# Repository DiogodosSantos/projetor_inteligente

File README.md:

# projetor_inteligente
Arquivos importantes e códigos-fonte do trabalho de conclusao de curso: Firefly.

Criadores:  Diogo Batista dos Santos & Eric Nozomi Tatsuta

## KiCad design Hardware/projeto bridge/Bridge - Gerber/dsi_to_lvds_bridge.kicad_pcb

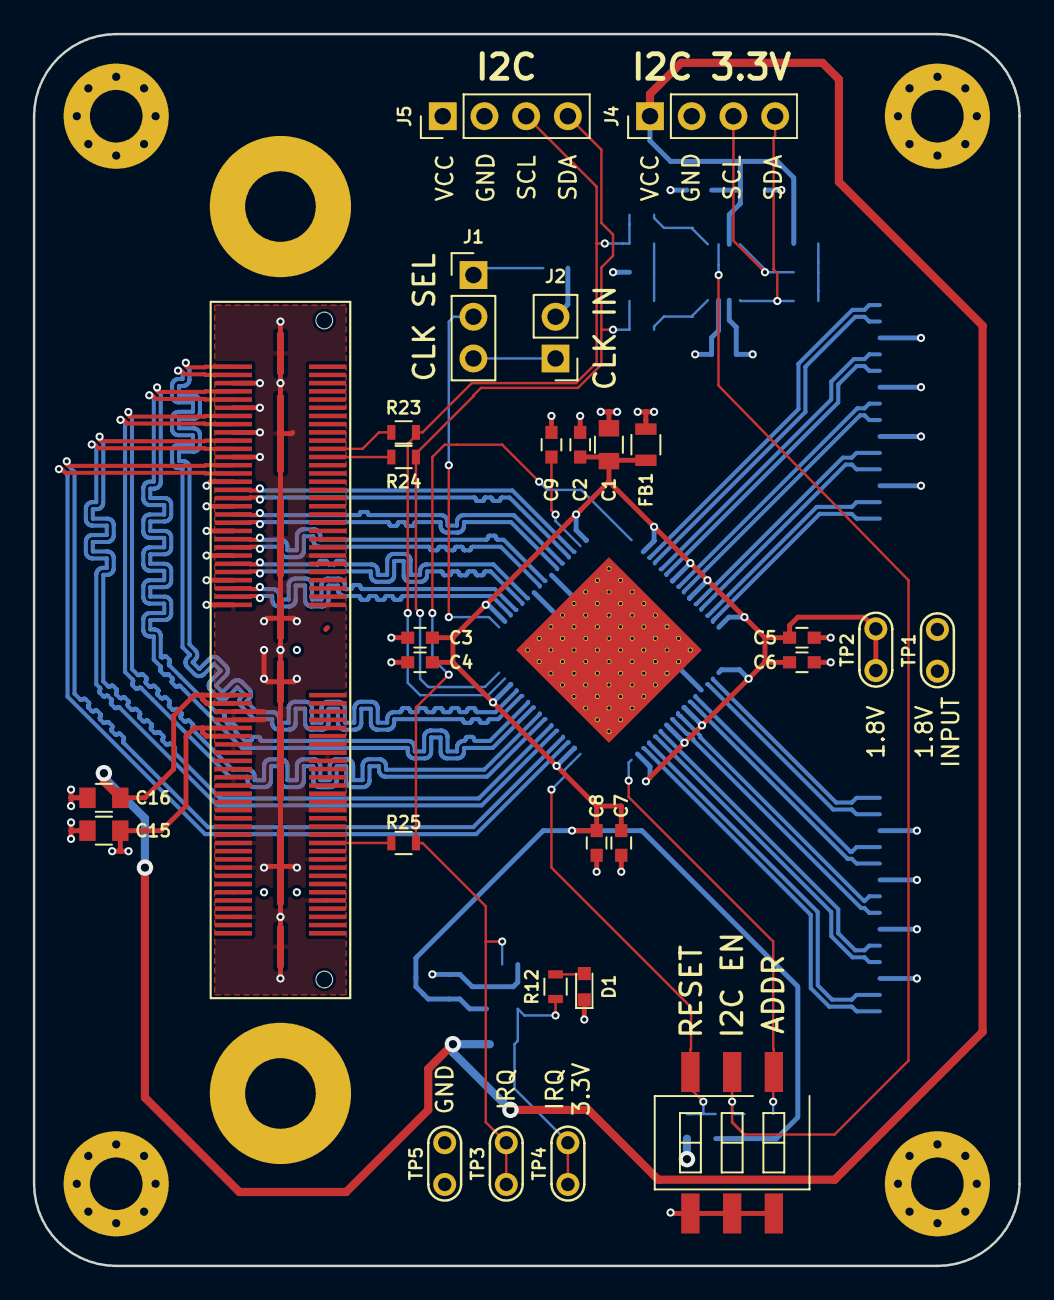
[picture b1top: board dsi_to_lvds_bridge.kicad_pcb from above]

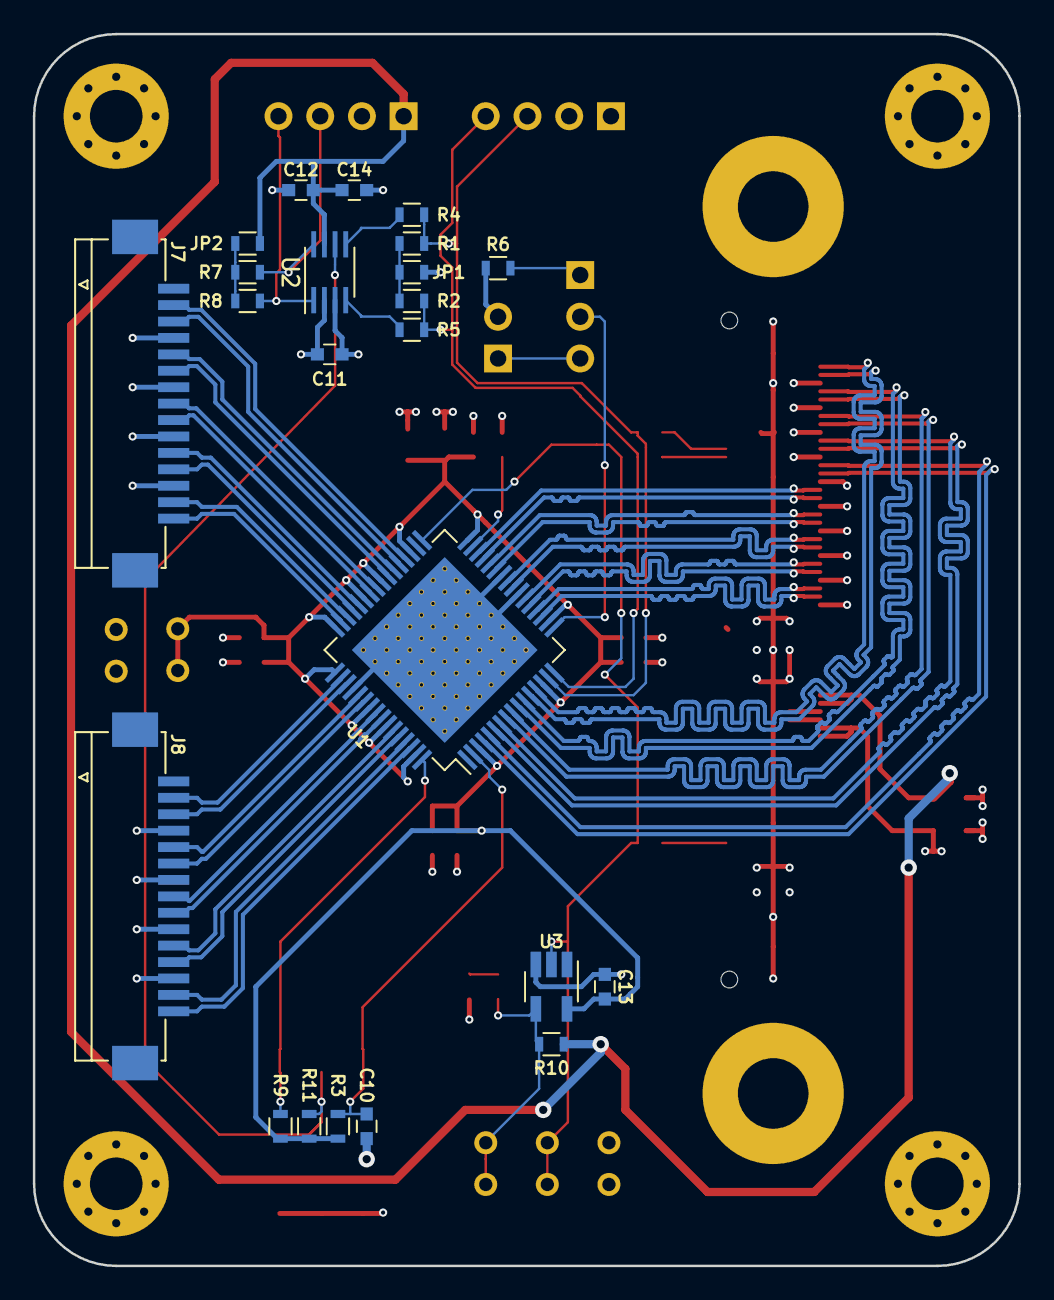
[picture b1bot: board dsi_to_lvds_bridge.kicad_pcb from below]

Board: 4 copper layers, 60.0 x 75.0 mm, 57 parts (23 on the bottom side), 65 nets.

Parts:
C1, C15, C16: 10µF; C_0805
C2, C9, C12: 1µF; C_0603
C3, C5, C7: 10nF; C_0603
C4, C6, C8, C11, C13, C14: 100nF; C_0603
C10: 220nF; C_0603
D1: LED; LED_0603
FB1: 220 @ 100MHz; L_0805
H1, H2, H3, H4: M3; MountingHole_3.2mm_M3_Pad_Via
H5, H6: 4.24; MountingHole_4.3mm_M4_Pad
J1: CLK_SEL; Pin_Header_Straight_1x03_Pitch2.54mm
J2: EXT_CLK; Pin_Header_Straight_1x02_Pitch2.54mm
J3: DIL6; SW_DIP_x3_W8.61mm_Slide_LowProfile
J4: I2C_3V3; Pin_Header_Straight_1x04_Pitch2.54mm
J5: I2C_1V8; Pin_Header_Straight_1x04_Pitch2.54mm
J6: QSH-060-01-X-D-A
J7: LVDS_A; 052271-1579
J8: LVDS_B; 052271-1579
JP1: I2C_PULL; R_0603
JP2: I2C_3V3_PULL; R_0603
R1, R2, R7, R8, R9, R11: 4.7K; R_0603
R3: R; R_0603
R4, R5, R12, R23, R24, R25: 0; R_0603
R6: 10K; R_0603
R10: 1K; R_0603
TP1: 1V8_IN; Test_Point
TP2: 1V8; Test_Point
TP3: IRQ; Test_Point
TP4: IRQ_3V3; Test_Point
TP5: GND; Test_Point
U1: SN65DSI85-Q1; HTQFP-64_1EP_10x10mm_Pitch0.5mm_ThermalPad
U2: TXS0102; SSOP-8_2.95x2.8mm_Pitch0.65mm
U3: SN74LVC1G07; SOT-23-5_HandSoldering

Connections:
+1V8: C1.1, C2.1, C3.1, C4.1, C5.1, C6.1, C7.1, C8.1, C13.1, FB1.2, R3.1, R9.1, R11.1, TP2.1, U1.3, U1.14, U1.18, U1.32, U1.35, U1.40, U1.43, U1.48, U1.49, U1.55, U1.58, U1.63, U3.5
+1V8_INPUT: C11.1, C15.1, FB1.1, J5.1, J6.69, J6.71, JP1.2, TP1.1, U2.3
+3V3: C12.1, C14.1, C16.1, J4.1, J6.61, J6.63, JP2.2, R10.1, U2.7
/ADDR: J3.1, R9.2, U1.64
/I2C_EN: J3.2, R11.2, U2.6
/REFCLK: J1.2, U1.17
DSI_A0_N: J6.55, U1.20
DSI_A0_P: J6.57, U1.19
DSI_A1_N: J6.49, U1.22
DSI_A1_P: J6.51, U1.21
DSI_A2_N: J6.37, U1.28
DSI_A2_P: J6.39, U1.27
DSI_A3_N: J6.31, U1.30
DSI_A3_P: J6.33, U1.29
DSI_ACLK_N: J6.43, U1.25
DSI_ACLK_P: J6.45, U1.24
DSI_B0_N: J6.25, U1.5
DSI_B0_P: J6.27, U1.4
DSI_B1_N: J6.19, U1.7
DSI_B1_P: J6.21, U1.6
DSI_B2_N: J6.7, U1.11
DSI_B2_P: J6.9, U1.10
DSI_B3_N: J6.1, U1.13
DSI_B3_P: J6.3, U1.12
DSI_BCLK_N: J6.13, U1.9
DSI_BCLK_P: J6.15, U1.8
GND: C1.2, C2.2, C3.2, C4.2, C5.2, C6.2, C7.2, C8.2, C9.2, C10.2, C11.2, C12.2, C13.2, C14.2, C15.2, C16.2, D1.1, H1.1, H2.1, H3.1, H4.1, J2.2, J3.4, J3.5, J3.6, J4.2, J5.2, J6.5, J6.11, J6.17, J6.23, J6.29, J6.35, J6.41, J6.47, J6.48, J6.52, J6.53, J6.59, J6.60, J6.65, J6.67, J6.70, J6.73, J6.75, J6.76, J6.78, J6.81, J6.83, J6.90, J6.91, J6.96, J6.97, J6.102, J6.103, J6.109, J6.112, J6.115, J6.121, J6.122, J6.123, J6.124, J6.125, J6.126, J6.127, J6.128, J7.4, J7.7, J7.10, J7.13, J8.4, J8.7, J8.10, J8.13, R6.1, TP5.1, U1.23, U1.26, U1.52, U1.65, U2.2, U3.3
I2C_3V3_SCL: J4.3, R7.2, U2.8
I2C_3V3_SDA: J4.4, R8.2, U2.1
I2C_SCL: J5.3, R1.2, R4.1, R23.2, U1.15
I2C_SDA: J5.4, R2.2, R5.2, R24.1, U1.16
IRQ: R25.2, TP3.1, U1.33, U3.2
IRQ_3V3: R10.2, R12.1, TP4.1, U3.4
LVDS_A0_N: J7.15, U1.47
LVDS_A0_P: J7.14, U1.46
LVDS_A1_N: J7.12, U1.45
LVDS_A1_P: J7.11, U1.44
LVDS_A2_N: J7.9, U1.42
LVDS_A2_P: J7.8, U1.41
LVDS_A3_N: J7.3, U1.37
LVDS_A3_P: J7.2, U1.36
LVDS_ACLK_N: J7.6, U1.39
LVDS_ACLK_P: J7.5, U1.38
LVDS_B0_N: J8.15, U1.62
LVDS_B0_P: J8.14, U1.61
LVDS_B1_N: J8.12, U1.60
LVDS_B1_P: J8.11, U1.59
LVDS_B2_N: J8.9, U1.57
LVDS_B2_P: J8.8, U1.56
LVDS_B3_N: J8.3, U1.51
LVDS_B3_P: J8.2, U1.50
LVDS_BCLK_N: J8.6, U1.54
LVDS_BCLK_P: J8.5, U1.53
unnamed: C9.1, U1.31
unnamed: D1.2, R12.2
unnamed: J1.1, R6.2
unnamed: J1.3, J2.1
unnamed: J6.22, R23.1
unnamed: J6.24, R24.2
unnamed: J6.98, R25.1
unnamed: JP1.1, R1.1, R2.1
unnamed: JP2.1, R7.1, R8.1
unnamed: R4.2, U2.5
unnamed: R5.1, U2.4
RESETN: C10.1, J3.3, R3.2, U1.2
